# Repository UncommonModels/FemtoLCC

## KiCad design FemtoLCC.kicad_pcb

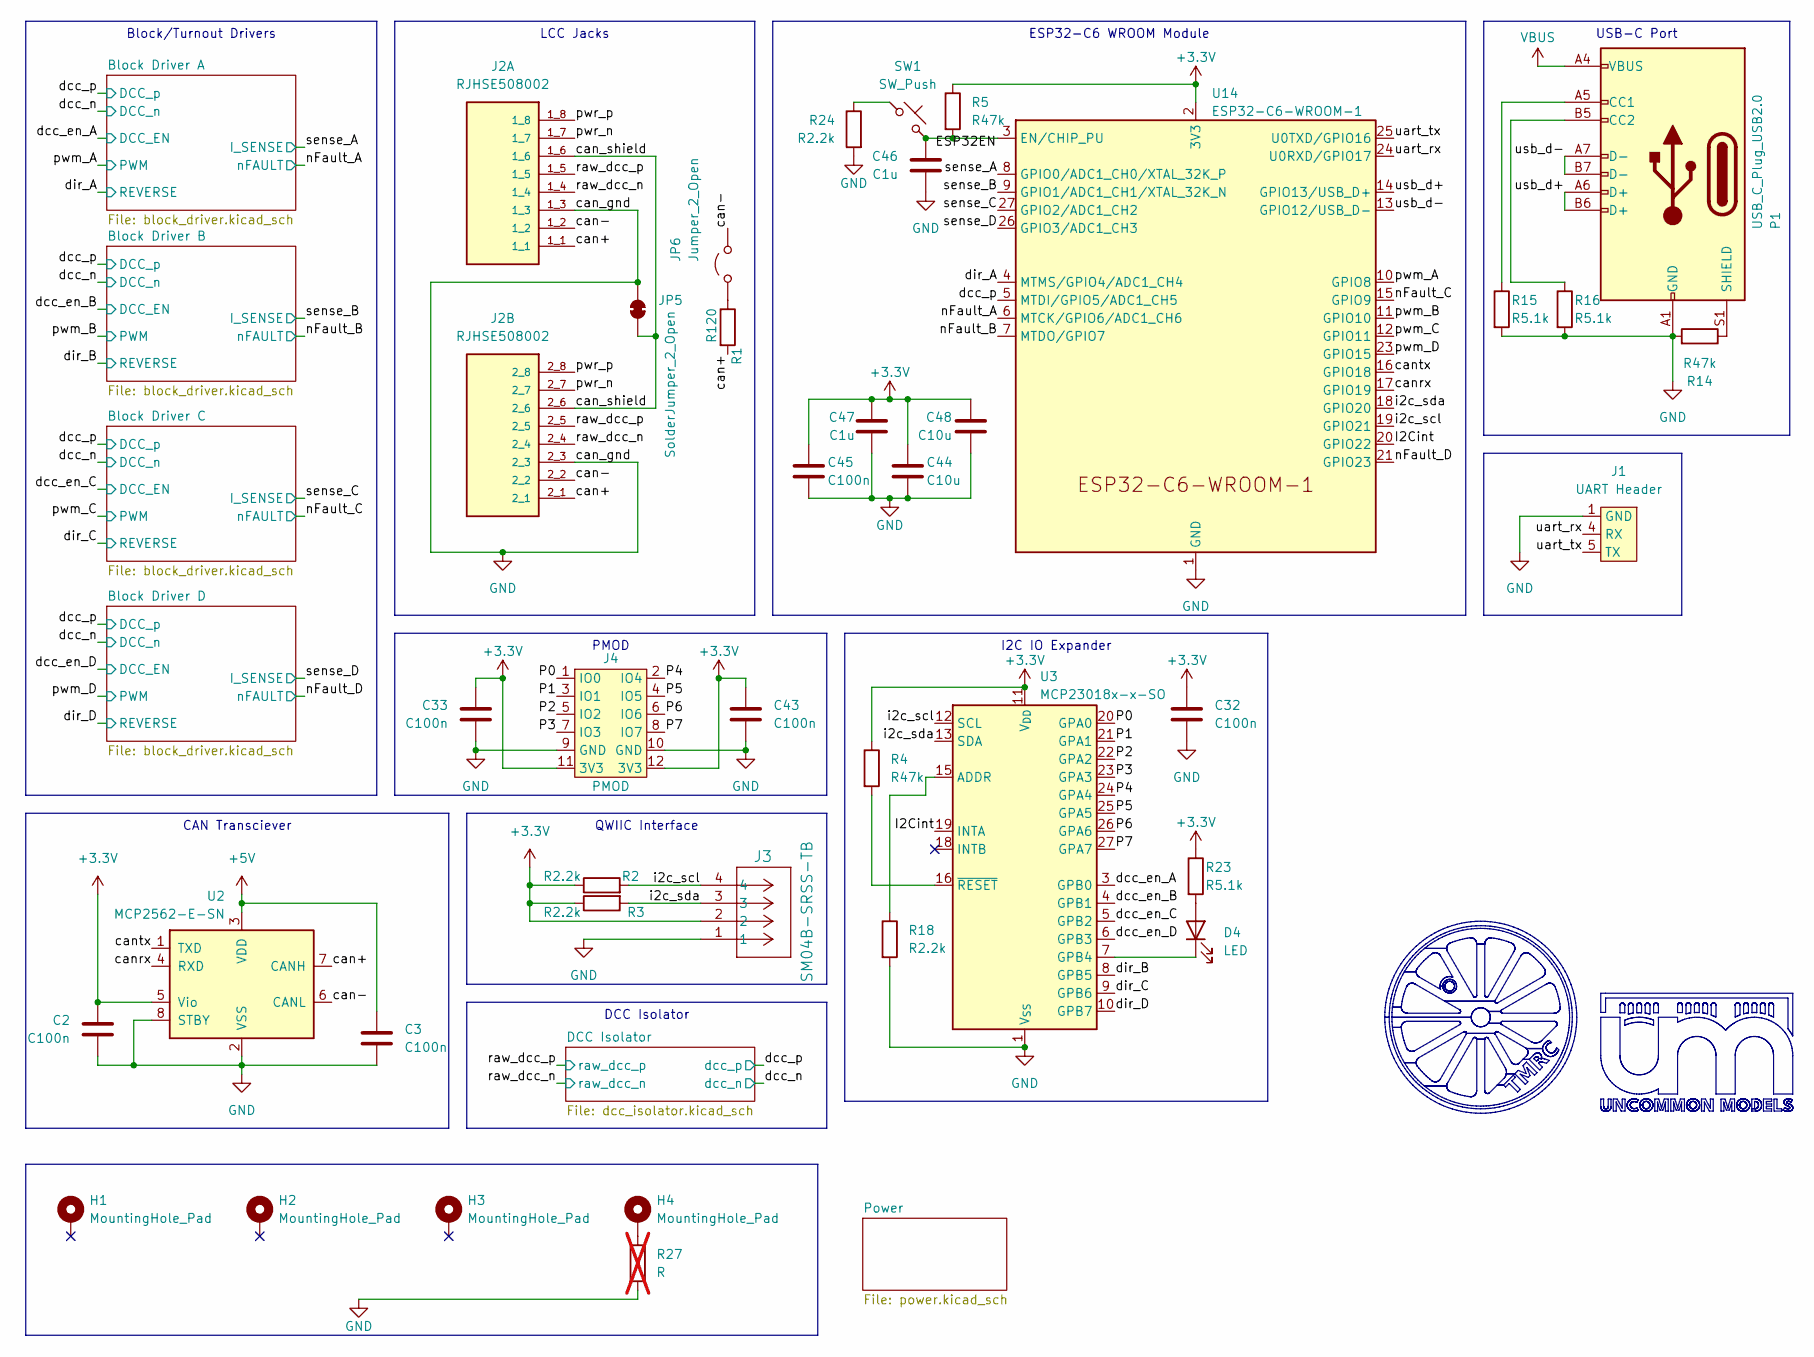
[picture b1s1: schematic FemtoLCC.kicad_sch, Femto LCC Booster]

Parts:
C2, C3, C32, C33, C43: C100n; C_0805_2012Metric_Pad1.18x1.45mm_HandSolder; Manufacturer Part Number CL21B104KACNFNC
C44, C48: C10u; C_1206_3216Metric_Pad1.33x1.80mm_HandSolder
C45: C100n; C_0805_2012Metric_Pad1.18x1.45mm_HandSolder
C46, C47: C1u; C_0805_2012Metric_Pad1.18x1.45mm_HandSolder
D4: LED; LED_0603_1608Metric
H1, H2, H3, H4: MountingHole_Pad; MountingHole_4.3mm_M4_Pad_Via
J1: UART Header; PinHeader_1x06_P2.54mm_Vertical
J2: RJHSE508002; AMPHENOL_RJHSE508002; PARTREV E
J3: SM04B-SRSS-TB; JST_SH_BM04B-SRSS-TB_1x04-1MP_P1.00mm_Vertical
J4: PMOD; PinSocket_2x06_P2.54mm_Horizontal
JP5: SolderJumper_2_Open; SolderJumper-2_P1.3mm_Bridged_RoundedPad1.0x1.5mm
JP6: Jumper_2_Open; TestPoint_2Pads_Pitch2.54mm_Drill0.8mm
P1: USB_C_Plug_USB2.0; USB_C_Receptacle_G-Switch_GT-USB-7051x
R1: R120; R_0805_2012Metric_Pad1.20x1.40mm_HandSolder; Manufacturer Part Number ERJ6ENF4702V
R2, R3, R18, R24: R2.2k; R_0402_1005Metric; Manufacturer Part Number ERJ6ENF4702V
R4: R47k; R_0805_2012Metric_Pad1.20x1.40mm_HandSolder; Manufacturer Part Number ERJ6ENF4702V
R5, R14: R47k; R_0402_1005Metric; Manufacturer Part Number ERJ6ENF4702V
R15, R16, R23: R5.1k; R_0402_1005Metric
R27: R; R_1206_3216Metric; not fitted
SW1: SW_Push; SW_Push_1P1T_XKB_TS-1187A
U2: MCP2562-E-SN; SOIC-8_3.9x4.9mm_P1.27mm; Manufacturer Part Number MCP2562-E-SN
U3: MCP23018x-x-SO; SOIC-28W_7.5x17.9mm_P1.27mm
U14: ESP32-C6-WROOM-1

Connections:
+3.3V: C2.1, C32.1, C33.1, C43.1, C44.1, C45.1, C47.2, C48.1, J3.2, J4.11 (3V3), J4.12 (3V3), R2.1, R3.1, R4.1, R5.1, R23.1, U2.5 (Vio), U3.11 (V_{DD}), U14.2 (3V3); also elsewhere on the board
+5V: C3.1, U2.3 (VDD); also elsewhere on the board
/ESP32EN: C46.2, R5.2, SW1.2, U14.3 (EN/CHIP_PU)
/I2Cint: U3.19 (INTA), U14.20 (GPIO22)
/P0: J4.1 (IO0), U3.20 (GPA0)
/P1: J4.3 (IO1), U3.21 (GPA1)
/P2: J4.5 (IO2), U3.22 (GPA2)
/P3: J4.7 (IO3), U3.23 (GPA3)
/P4: J4.2 (IO4), U3.24 (GPA4)
/P5: J4.4 (IO5), U3.25 (GPA5)
/P6: J4.6 (IO6), U3.26 (GPA6)
/P7: J4.8 (IO7), U3.27 (GPA7)
/can+: J2.1_1, J2.2_1, R1.2, U2.7 (CANH)
/can-: J2.1_2, J2.2_2, JP6.2 (B), U2.6 (CANL)
/can_shield: J2.1_6, J2.2_6, JP5.1 (A)
/canrx: U2.4 (RXD), U14.17 (GPIO19)
/cantx: U2.1 (TXD), U14.16 (GPIO18)
/dcc_en_A: U3.3 (GPB0); also elsewhere on the board
/dcc_en_B: U3.4 (GPB1); also elsewhere on the board
/dcc_en_C: U3.5 (GPB2); also elsewhere on the board
/dcc_en_D: U3.6 (GPB3); also elsewhere on the board
/dcc_p: U14.5 (MTDI/GPIO5/ADC1_CH5); also elsewhere on the board
/dir_A: U14.4 (MTMS/GPIO4/ADC1_CH4); also elsewhere on the board
/dir_B: U3.8 (GPB5); also elsewhere on the board
/dir_C: U3.9 (GPB6); also elsewhere on the board
/dir_D: U3.10 (GPB7); also elsewhere on the board
/i2c_scl: J3.4, R2.2, U3.12 (SCL), U14.19 (GPIO21)
/i2c_sda: J3.3, R3.2, U3.13 (SDA), U14.18 (GPIO20)
/nFault_A: U14.6 (MTCK/GPIO6/ADC1_CH6); also elsewhere on the board
/nFault_B: U14.7 (MTDO/GPIO7); also elsewhere on the board
/nFault_C: U14.15 (GPIO9); also elsewhere on the board
/nFault_D: U14.21 (GPIO23); also elsewhere on the board
/pwm_A: U14.10 (GPIO8); also elsewhere on the board
/pwm_B: U14.11 (GPIO10); also elsewhere on the board
/pwm_C: U14.12 (GPIO11); also elsewhere on the board
/pwm_D: U14.23 (GPIO15); also elsewhere on the board
/pwr_n: J2.1_7, J2.2_7
/pwr_p: J2.1_8, J2.2_8
/raw_dcc_n: J2.1_4, J2.2_4; also elsewhere on the board
/raw_dcc_p: J2.1_5, J2.2_5; also elsewhere on the board
/sense_A: U14.8 (GPIO0/ADC1_CH0/XTAL_32K_P); also elsewhere on the board
/sense_B: U14.9 (GPIO1/ADC1_CH1/XTAL_32K_N); also elsewhere on the board
/sense_C: U14.27 (GPIO2/ADC1_CH2); also elsewhere on the board
/sense_D: U14.26 (GPIO3/ADC1_CH3); also elsewhere on the board
/uart_rx: J1.4 (RX), U14.24 (U0RXD/GPIO17)
/uart_tx: J1.5 (TX), U14.25 (U0TXD/GPIO16)
/usb_d+: P1.A6 (D+), P1.B6 (D+), U14.14 (GPIO13/USB_D+)
/usb_d-: P1.A7 (D-), P1.B7 (D-), U14.13 (GPIO12/USB_D-)
GND: C2.2, C3.2, C32.2, C33.2, C43.2, C44.2, C45.2, C46.1, C47.1, C48.2, J1.1 (GND), J2.1_3, J2.2_3, J3.1, J4.9 (GND), J4.10 (GND), JP5.2 (B), P1.A1 (GND), P1.A12 (GND), P1.B1 (GND), P1.B12 (GND), R14.2, R15.2, R16.2, R18.2, R24.2, R27.2, U2.2 (VSS), U2.8 (STBY), U3.1 (V_{SS}), U14.1 (GND), U14.28 (GND), U14.29 (GND); also elsewhere on the board
unnamed: D4.2 (A), R23.2
unnamed: D4.1 (K), U3.7 (GPB4)
unnamed: H4.1 (1_1), R27.1
unnamed: JP6.1 (A), R1.1
unnamed: P1.A5 (CC1), R15.1
unnamed: P1.B5 (CC2), R16.1
unnamed: P1.S1 (SHIELD), R14.1
unnamed: R24.1, SW1.1
unnamed: R18.1, U3.15 (ADDR)
unnamed: R4.2, U3.16 (~RESET)
VBUS: P1.A4 (VBUS), P1.A9 (VBUS), P1.B4 (VBUS), P1.B9 (VBUS); also elsewhere on the board

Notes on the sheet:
PMOD
CAN Transciever
I2C IO Expander
Block/Turnout Drivers
DCC Isolator
USB-C Port
QWIIC Interface
LCC Jacks
ESP32-C6 WROOM Module

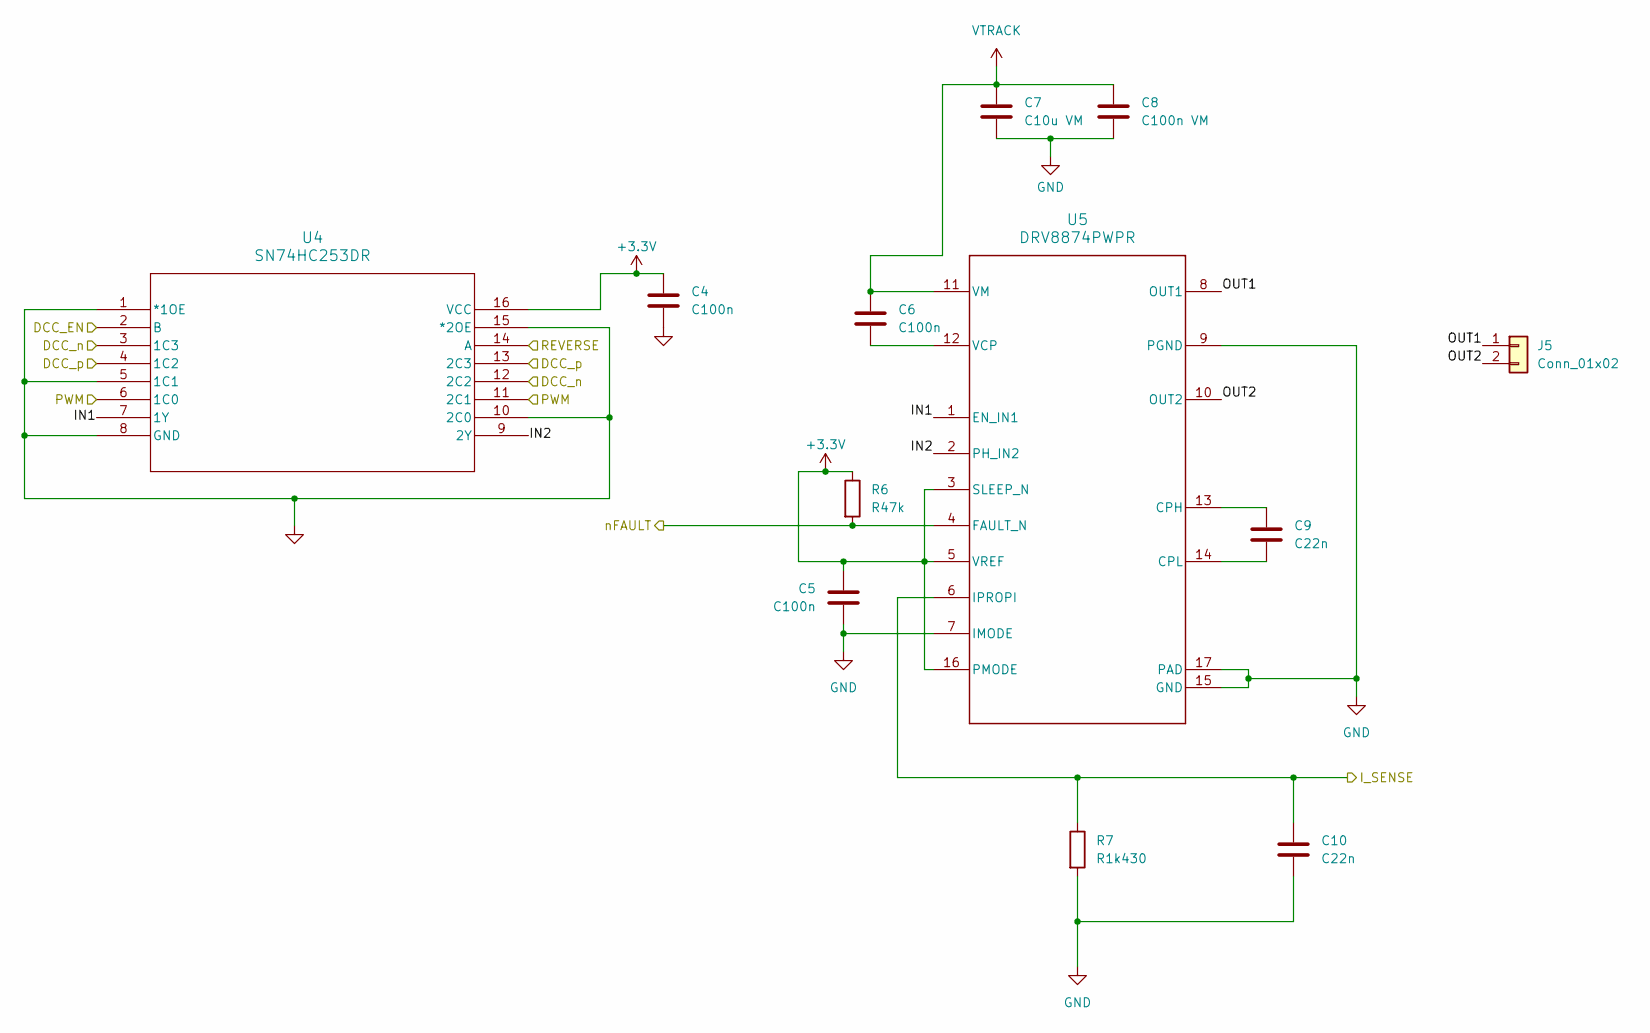
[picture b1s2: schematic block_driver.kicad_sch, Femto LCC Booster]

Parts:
C4, C5, C6: C100n; C_0805_2012Metric_Pad1.18x1.45mm_HandSolder; Manufacturer Part Number CL21B104KACNFNC
C7: C10u VM; C_1206_3216Metric_Pad1.33x1.80mm_HandSolder; Manufacturer Part Number CL31A106KBHNNNE
C8: C100n VM; C_0805_2012Metric_Pad1.18x1.45mm_HandSolder; Manufacturer Part Number CL21B104KBFXPJE
C9, C10: C22n; C_0805_2012Metric_Pad1.18x1.45mm_HandSolder; Manufacturer Part Number CL21B223JBANNNC
J5: Conn_01x02; TerminalBlock_Phoenix_MKDS-1,5-2-5.08_1x02_P5.08mm_Horizont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
R6: R47k; R_0805_2012Metric_Pad1.20x1.40mm_HandSolder; Manufacturer Part Number ERJ6ENF4702V
R7: R1k430; R_0805_2012Metric_Pad1.20x1.40mm_HandSolder; Manufacturer Part Number RC0805FR-071K43L
U4: SN74HC253DR; SO-16_3.9x9.9mm_P1.27mm; Manufacturer Part Number SN74HC253DR
U5: DRV8874PWPR; PWP0016J_NV; Manufacturer Part Number DRV8874PWPR

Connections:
+3.3V: C4.1, C5.1, R6.1, U4.16 (VCC), U5.3 (SLEEP_N), U5.5 (VREF), U5.16 (PMODE); also elsewhere on the board
/Block Driver A/IN1: U4.7 (1Y), U5.1 (EN_IN1)
/Block Driver A/IN2: U4.9 (2Y), U5.2 (PH_IN2)
/Block Driver A/OUT1: J5.1, U5.8 (OUT1)
/Block Driver A/OUT2: J5.2, U5.10 (OUT2)
/dcc_en_A: U4.2 (B); also elsewhere on the board
/dcc_n: U4.3 (1C3), U4.12 (2C2); also elsewhere on the board
/dcc_p: U4.4 (1C2), U4.13 (2C3); also elsewhere on the board
/dir_A: U4.14 (A); also elsewhere on the board
/nFault_A: R6.2, U5.4 (FAULT_N); also elsewhere on the board
/pwm_A: U4.6 (1C0), U4.11 (2C1); also elsewhere on the board
/sense_A: C10.1, R7.1, U5.6 (IPROPI); also elsewhere on the board
GND: C4.2, C5.2, C7.2, C8.2, C10.2, R7.2, U4.1 (*1OE), U4.5 (1C1), U4.8 (GND), U4.10 (2C0), U4.15 (*2OE), U5.7 (IMODE), U5.9 (PGND), U5.15 (GND), U5.17 (PAD); also elsewhere on the board
unnamed: C9.1, U5.13 (CPH)
unnamed: C9.2, U5.14 (CPL)
unnamed: C6.2, U5.12 (VCP)
VTRACK: C6.1, C7.1, C8.1, U5.11 (VM); also elsewhere on the board

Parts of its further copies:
C11, C12, C13, C18, C19, C20, C25, C26, C27: C100n; C_0805_2012Metric_Pad1.18x1.45mm_HandSolder; Manufacturer Part Number CL21B104KACNFNC
C14, C21, C28: C10u VM; C_1206_3216Metric_Pad1.33x1.80mm_HandSolder; Manufacturer Part Number CL31A106KBHNNNE
C15, C22, C29: C100n VM; C_0805_2012Metric_Pad1.18x1.45mm_HandSolder; Manufacturer Part Number CL21B104KBFXPJE
C16, C17, C23, C24, C30, C31: C22n; C_0805_2012Metric_Pad1.18x1.45mm_HandSolder; Manufacturer Part Number CL21B223JBANNNC
J6, J7, J8: Conn_01x02; TerminalBlock_Phoenix_MKDS-1,5-2-5.08_1x02_P5.08mm_Horizont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
R8, R10, R12: R47k; R_0805_2012Metric_Pad1.20x1.40mm_HandSolder; Manufacturer Part Number ERJ6ENF4702V
R9, R11, R13: R1k430; R_0805_2012Metric_Pad1.20x1.40mm_HandSolder; Manufacturer Part Number RC0805FR-071K43L
U6, U8, U10: SN74HC253DR; SO-16_3.9x9.9mm_P1.27mm; Manufacturer Part Number SN74HC253DR
U7, U9, U11: DRV8874PWPR; PWP0016J_NV; Manufacturer Part Number DRV8874PWPR

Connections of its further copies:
+3.3V: C11.1, C12.1, C18.1, C19.1, C25.1, C26.1, R8.1, R10.1, R12.1, U6.16 (VCC), U7.3 (SLEEP_N), U7.5 (VREF), U7.16 (PMODE), U8.16 (VCC), U9.3 (SLEEP_N), U9.5 (VREF), U9.16 (PMODE), U10.16 (VCC), U11.3 (SLEEP_N), U11.5 (VREF), U11.16 (PMODE); also elsewhere on the board
/Block Driver B/IN1: U6.7 (1Y), U7.1 (EN_IN1)
/Block Driver B/IN2: U6.9 (2Y), U7.2 (PH_IN2)
/Block Driver B/OUT1: J6.1, U7.8 (OUT1)
/Block Driver B/OUT2: J6.2, U7.10 (OUT2)
/Block Driver C/IN1: U8.7 (1Y), U9.1 (EN_IN1)
/Block Driver C/IN2: U8.9 (2Y), U9.2 (PH_IN2)
/Block Driver C/OUT1: J7.1, U9.8 (OUT1)
/Block Driver C/OUT2: J7.2, U9.10 (OUT2)
/Block Driver D/IN1: U10.7 (1Y), U11.1 (EN_IN1)
/Block Driver D/IN2: U10.9 (2Y), U11.2 (PH_IN2)
/Block Driver D/OUT1: J8.1, U11.8 (OUT1)
/Block Driver D/OUT2: J8.2, U11.10 (OUT2)
/dcc_en_B: U6.2 (B); also elsewhere on the board
/dcc_en_C: U8.2 (B); also elsewhere on the board
/dcc_en_D: U10.2 (B); also elsewhere on the board
/dcc_n: U6.3 (1C3), U6.12 (2C2), U8.3 (1C3), U8.12 (2C2), U10.3 (1C3), U10.12 (2C2); also elsewhere on the board
/dcc_p: U6.4 (1C2), U6.13 (2C3), U8.4 (1C2), U8.13 (2C3), U10.4 (1C2), U10.13 (2C3); also elsewhere on the board
/dir_B: U6.14 (A); also elsewhere on the board
/dir_C: U8.14 (A); also elsewhere on the board
/dir_D: U10.14 (A); also elsewhere on the board
/nFault_B: R8.2, U7.4 (FAULT_N); also elsewhere on the board
/nFault_C: R10.2, U9.4 (FAULT_N); also elsewhere on the board
/nFault_D: R12.2, U11.4 (FAULT_N); also elsewhere on the board
/pwm_B: U6.6 (1C0), U6.11 (2C1); also elsewhere on the board
/pwm_C: U8.6 (1C0), U8.11 (2C1); also elsewhere on the board
/pwm_D: U10.6 (1C0), U10.11 (2C1); also elsewhere on the board
/sense_B: C17.1, R9.1, U7.6 (IPROPI); also elsewhere on the board
/sense_C: C24.1, R11.1, U9.6 (IPROPI); also elsewhere on the board
/sense_D: C31.1, R13.1, U11.6 (IPROPI); also elsewhere on the board
GND: C11.2, C12.2, C14.2, C15.2, C17.2, C18.2, C19.2, C21.2, C22.2, C24.2, C25.2, C26.2, C28.2, C29.2, C31.2, R9.2, R11.2, R13.2, U6.1 (*1OE), U6.5 (1C1), U6.8 (GND), U6.10 (2C0), U6.15 (*2OE), U7.7 (IMODE), U7.9 (PGND), U7.15 (GND), U7.17 (PAD), U8.1 (*1OE), U8.5 (1C1), U8.8 (GND), U8.10 (2C0), U8.15 (*2OE), U9.7 (IMODE), U9.9 (PGND), U9.15 (GND), U9.17 (PAD), U10.1 (*1OE), U10.5 (1C1), U10.8 (GND), U10.10 (2C0), U10.15 (*2OE), U11.7 (IMODE), U11.9 (PGND), U11.15 (GND), U11.17 (PAD); also elsewhere on the board
unnamed: C16.1, U7.13 (CPH)
unnamed: C16.2, U7.14 (CPL)
unnamed: C13.2, U7.12 (VCP)
unnamed: C23.1, U9.13 (CPH)
unnamed: C23.2, U9.14 (CPL)
unnamed: C20.2, U9.12 (VCP)
unnamed: C30.1, U11.13 (CPH)
unnamed: C30.2, U11.14 (CPL)
unnamed: C27.2, U11.12 (VCP)
VTRACK: C13.1, C14.1, C15.1, C20.1, C21.1, C22.1, C27.1, C28.1, C29.1, U7.11 (VM), U9.11 (VM), U11.11 (VM); also elsewhere on the board

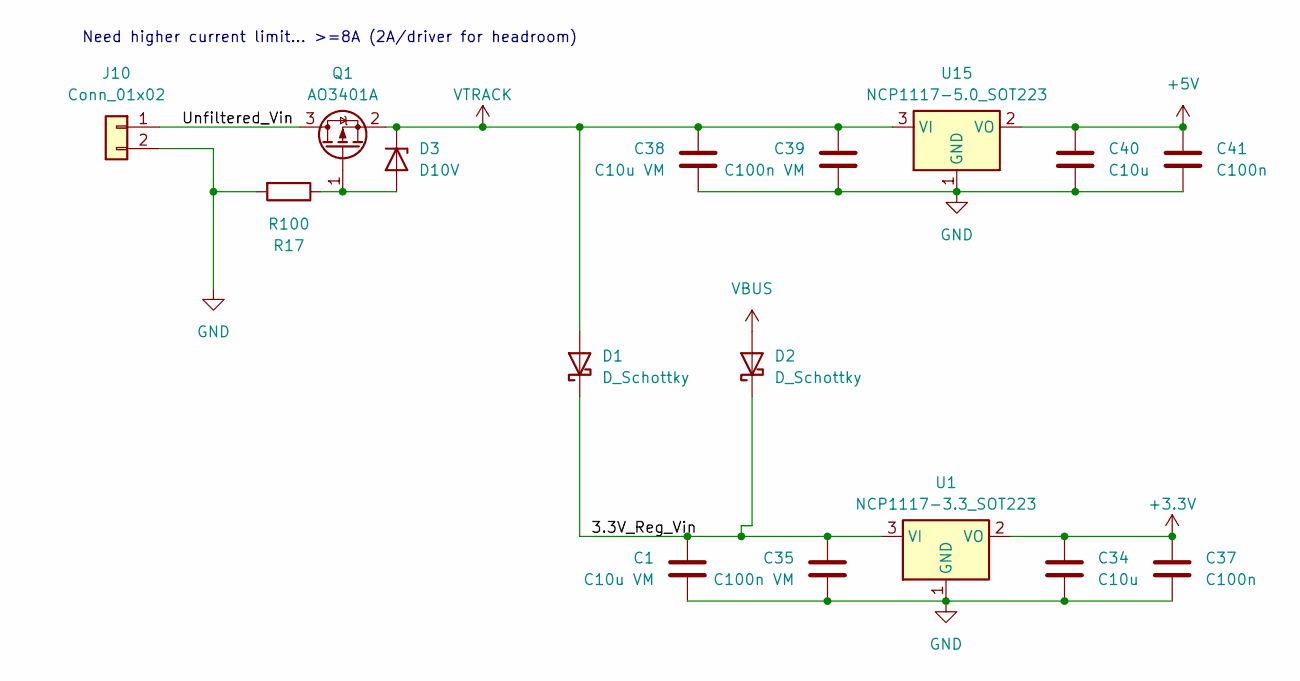
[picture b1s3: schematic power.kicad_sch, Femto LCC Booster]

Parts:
C1, C38: C10u VM; C_1206_3216Metric_Pad1.33x1.80mm_HandSolder
C34, C40: C10u; C_1206_3216Metric_Pad1.33x1.80mm_HandSolder
C35, C39: C100n VM; C_0805_2012Metric_Pad1.18x1.45mm_HandSolder
C37, C41: C100n; C_0805_2012Metric_Pad1.18x1.45mm_HandSolder
D1, D2: D_Schottky; D_SMA_Handsoldering
D3: D10V; D_SOD-323_HandSoldering
J10: Conn_01x02; PhoenixContact_MCV_1,5_2-G-3.5_1x02_P3.50mm_Vertical
Q1: AO3401A; SOT-23
R17: R100; R_0402_1005Metric
U1: NCP1117-3.3_SOT223; SOT-223-3_TabPin2
U15: NCP1117-5.0_SOT223; SOT-223-3_TabPin2

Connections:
+3.3V: C34.1, C37.1, U1.2 (VO); also elsewhere on the board
+5V: C40.1, C41.1, U15.2 (VO); also elsewhere on the board
/Power/3.3V_Reg_Vin: C1.1, C35.1, D1.1 (K), D2.1 (K), U1.3 (VI)
/Power/Unfiltered_Vin: J10.1, Q1.3 (D)
GND: C1.2, C34.2, C35.2, C37.2, C38.2, C39.2, C40.2, C41.2, J10.2, R17.2, U1.1 (GND), U15.1 (GND); also elsewhere on the board
unnamed: D3.2 (A), Q1.1 (G), R17.1
VBUS: D2.2 (A); also elsewhere on the board
VTRACK: C38.1, C39.1, D1.2 (A), D3.1 (K), Q1.2 (S), U15.3 (VI); also elsewhere on the board

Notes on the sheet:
Need higher current limit... >=8A (2A/driver for headroom)

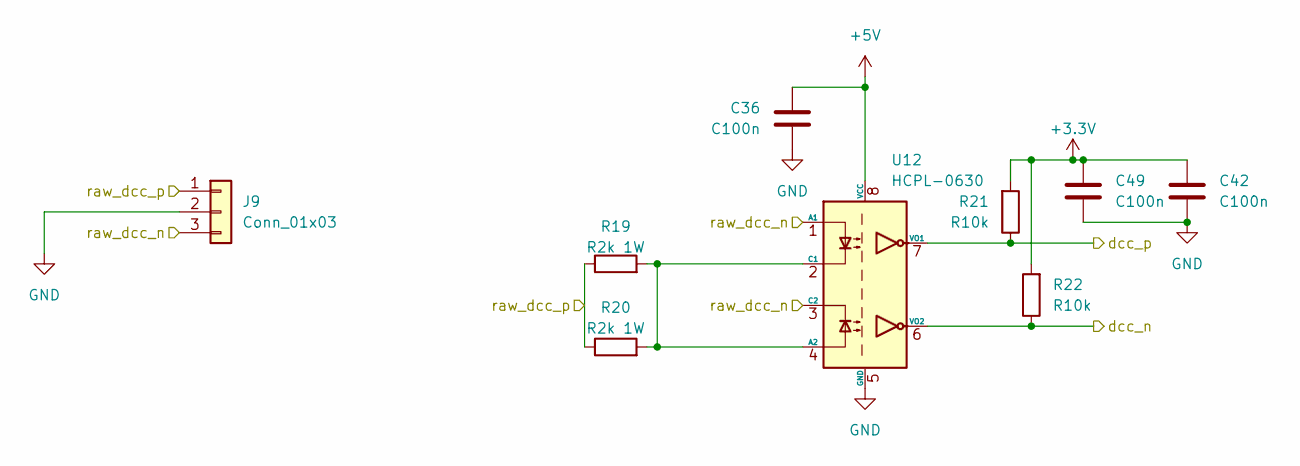
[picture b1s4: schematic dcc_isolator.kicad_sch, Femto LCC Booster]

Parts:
C36, C42, C49: C100n; C_0805_2012Metric_Pad1.18x1.45mm_HandSolder; Manufacturer Part Number CL21B104KACNFNC
J9: Conn_01x03; PhoenixContact_MCV_1,5_3-G-3.5_1x03_P3.50mm_Vertical
R19, R20: R2k 1W; R_2512_6332Metric_Pad1.40x3.35mm_HandSolder; Manufacturer Part Number AC2512JK-072KL
R21, R22: R10k; R_0805_2012Metric_Pad1.20x1.40mm_HandSolder; Manufacturer Part Number RC0805JR-0710KL
U12: HCPL-0630; SOIC-8_3.9x4.9mm_P1.27mm

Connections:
+3.3V: C42.1, C49.1, R21.2, R22.2; also elsewhere on the board
+5V: C36.1, U12.8 (VCC); also elsewhere on the board
/dcc_n: R22.1, U12.6 (VO2); also elsewhere on the board
/dcc_p: R21.1, U12.7 (VO1); also elsewhere on the board
/raw_dcc_n: J9.3, U12.1 (A1), U12.3 (C2); also elsewhere on the board
/raw_dcc_p: J9.1, R19.1, R20.1; also elsewhere on the board
GND: C36.2, C42.2, C49.2, J9.2, U12.5 (GND); also elsewhere on the board
unnamed: R19.2, R20.2, U12.2 (C1), U12.4 (A2)

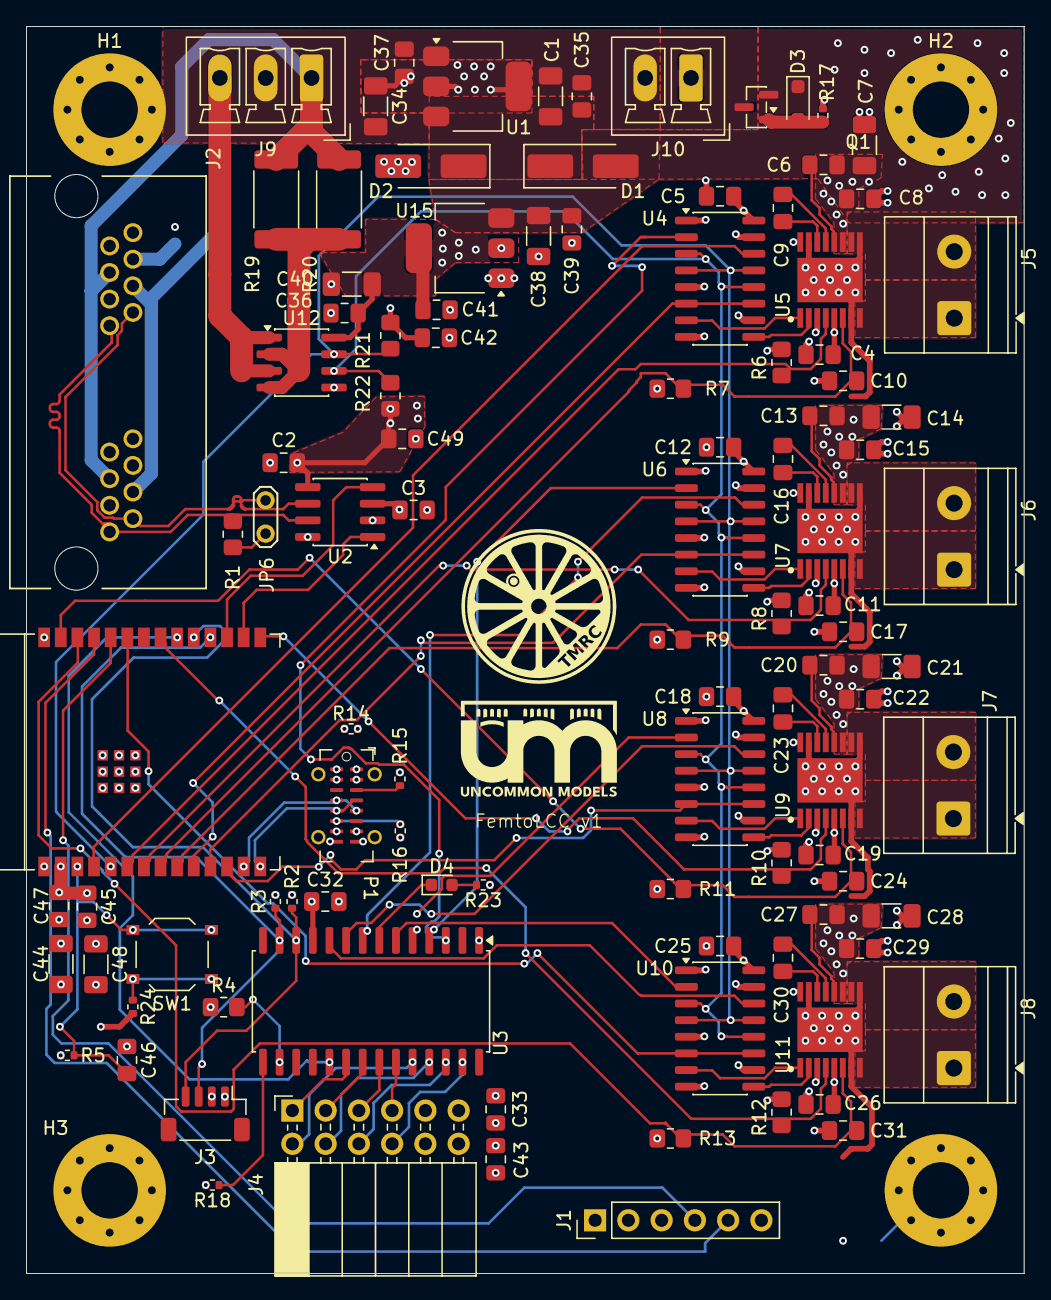
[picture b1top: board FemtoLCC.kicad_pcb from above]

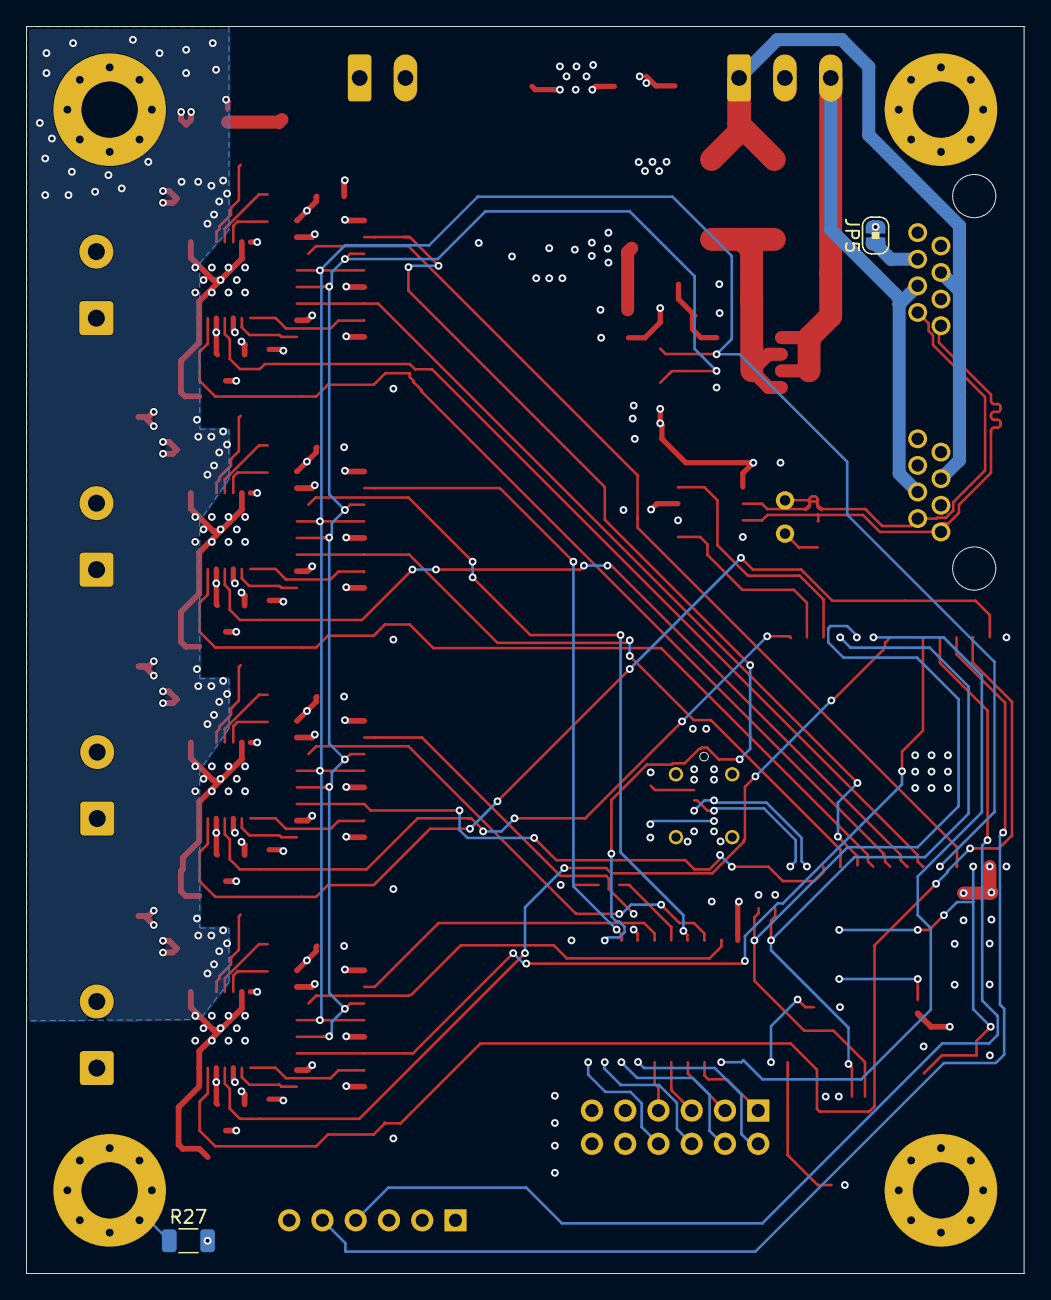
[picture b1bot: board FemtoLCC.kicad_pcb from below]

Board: 4 copper layers, 76.2 x 95.2 mm, 111 parts (2 on the bottom side), 94 nets.

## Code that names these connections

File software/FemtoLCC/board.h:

// FemtoLCC board pin map.
//
// Every assignment here was read out of the netlist in FemtoLCC.kicad_pcb, not
// transcribed by hand. Net names from the schematic are given alongside so the
// two can be checked against each other.
//
//   Uncommon Models — https://uncommonmodels.com

#pragma once

#include <stdint.h>

// ---------------------------------------------------------------------------
// LCC / CAN bus  — MCP2562 transceiver out to the dual-port RJ45 at J2
// ---------------------------------------------------------------------------
static const int PIN_CAN_TX = 18;   // /cantx
static const int PIN_CAN_RX = 19;   // /canrx

// LCC runs at 125 kbit/s. This is fixed by the standard; do not change it.
static const uint32_t LCC_BITRATE = 125000;

// ---------------------------------------------------------------------------
// DCC input — HCPL-0630 optocoupler, track side is galvanically isolated
// ---------------------------------------------------------------------------
static const int PIN_DCC_IN = 5;    // /dcc_p, the positive half of the opto pair

// ---------------------------------------------------------------------------
// I2C — MCP23018 port expander at U3
// ---------------------------------------------------------------------------
static const int PIN_I2C_SDA = 20;  // /i2c_sda
static const int PIN_I2C_SCL = 21;  // /i2c_scl
static const int PIN_I2C_INT = 22;  // /I2Cint, INTA from the expander

// The MCP23018 address is strapped by the ADDR pin. 0x20 is the base address.
static const uint8_t MCP23018_ADDR = 0x20;

// ---------------------------------------------------------------------------
// UART — 6-pin programming and console header J1
// ---------------------------------------------------------------------------
static const int PIN_UART_TX = 16;  // /uart_tx
static const int PIN_UART_RX = 17;  // /uart_rx

// ---------------------------------------------------------------------------
// Block driver channels
//
// Each channel is an SN74HC253 dual 4:1 multiplexer feeding a DRV8874 H-bridge.
// The multiplexer decides what reaches the driver:
//
//   dcc_en  dir  |  IN1        IN2        meaning
//   -------------+----------------------------------------------------------
//      0      0  |  pwm        (low)      DC drive, forward
//      0      1  |  (low)      pwm        DC drive, reverse
//      1      0  |  dcc_p      dcc_n      DCC pass-through, normal polarity
//      1      1  |  dcc_n      dcc_p      DCC pass-through, reversed polarity
//
// So dcc_en picks the mode and dir picks direction (DC) or phase (DCC). The
// reversed-polarity case is what lets a block act as a reversing section.
//
// pwm and sense are on the ESP32 for all four channels. dir is on the ESP32 for
// channel A only; B, C and D live on the expander, as do all four dcc_en lines.
// ---------------------------------------------------------------------------
static const int NUM_CHANNELS = 4;

// PWM into the multiplexer's C0/C1 inputs — /pwm_A … /pwm_D
static const int PIN_PWM[NUM_CHANNELS]     = { 8, 10, 11, 15 };

// DRV8874 IPROPI current sense, on ADC1 — /sense_A … /sense_D
static const int PIN_SENSE[NUM_CHANNELS]   = { 0, 1, 2, 3 };

// DRV8874 nFAULT, open drain, active low — /nFault_A … /nFault_D
static const int PIN_NFAULT[NUM_CHANNELS]  = { 6, 7, 9, 23 };

// Channel A's direction line is wired straight to the ESP32; -1 means the
// channel's dir line is on the expander instead.
static const int PIN_DIR_A = 4;             // /dir_A
static const int PIN_DIR[NUM_CHANNELS]     = { PIN_DIR_A, -1, -1, -1 };

// MCP23018 port B bit positions.
static const uint8_t EXP_DCC_EN_BIT[NUM_CHANNELS] = { 0, 1, 2, 3 };  // GPB0..GPB3
static const uint8_t EXP_DIR_BIT[NUM_CHANNELS]    = { 0xFF, 5, 6, 7 };// GPB5..GPB7
static const uint8_t EXP_LED_BIT = 4;                                 // GPB4 -> D4

// Port A (GPA0..GPA7) is uncommitted general-purpose I/O, brought out as /P0../P7.
static const uint8_t EXP_GPIO_COUNT = 8;

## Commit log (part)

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2026-04-15 Add new routing strategy
